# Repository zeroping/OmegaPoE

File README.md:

# OmegaPoE
A Power-over-Ethernet Dock for the Onion Omega board

This is a KiCad circut board design for an Onion Omega "dock" that connects the Onion via Ethernet, while also powering it via 802.3af Power-over-Ethernet.

The Onion Omega is a cheap ($10.75) linux single-board computer, and supports WiFi and Ethernet. For more information on the Onion Omega, see [the Onion Omega site](http://onion.io/omega2/).

This board is designed to be as small as possible while still providing an isolated 15-watt PoE supply. The 48 VDC power from PoE is converted into 12 V using a TI LM5070 in a flyback configuration. The 12 V is further stepped down to 5 V and 3.3 V using two TPS62135x DC-DC buck converters. 12 V was chosen to allow running 12V perhierals off of the board, such as 12V LED lighing strips. 

## Status
Four prototype boards have been built, and they work. There are some issues to work out and fixes to commit, but here's the v1 board run:

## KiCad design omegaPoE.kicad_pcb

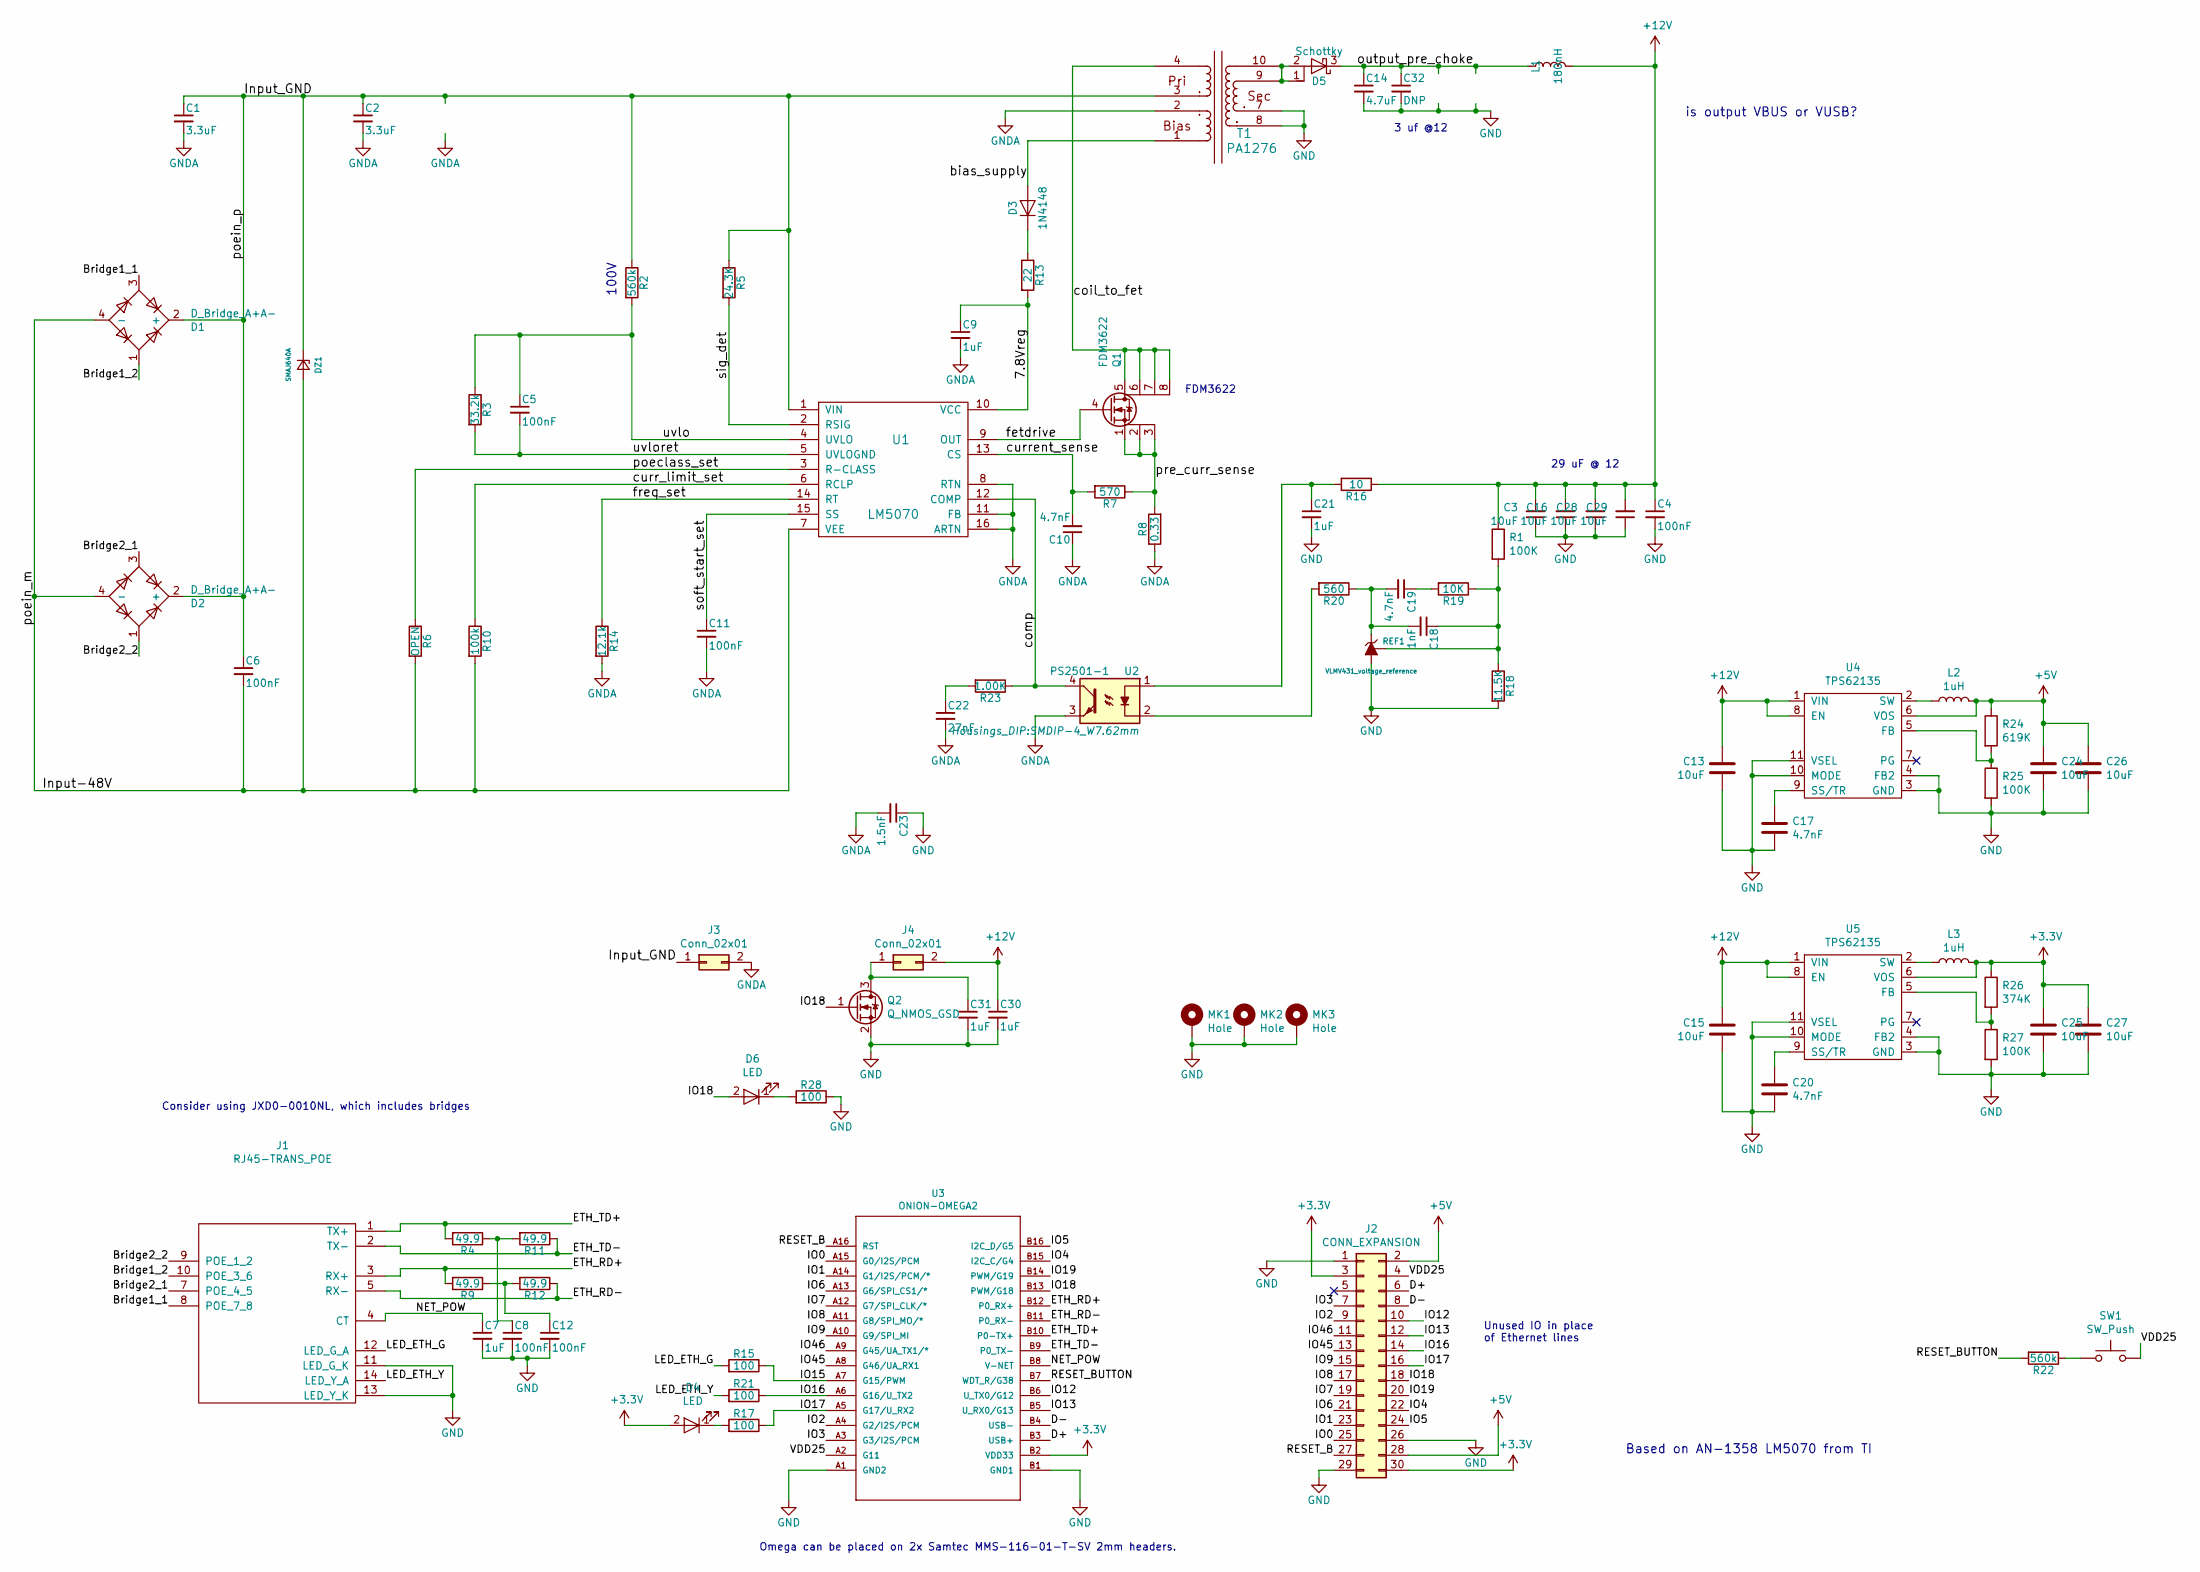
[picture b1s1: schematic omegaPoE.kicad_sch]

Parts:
C1, C2: 3.3uF; C_1206; MPN C3216X7S2A335K160AB
C3, C13, C15, C16, C24, C25, C26, C27, C28, C29: 10uF; C_1206; MPN MF-CAP-1206-10uF
C4, C5, C8, C11, C12: 100nF; C_0402; MPN MF-CAP-0402-0.1uF
C6: 100nF; C_1206; MPN 12061C104MAT4A
C7, C9, C21, C30, C31: 1uF; C_0402; MPN MF-CAP-0402-1uF
C10, C19: 4.7nF; C_0402; MPN MF-CAP-0402-4.7nF
C14: 4.7uF; C_0805; MPN EMK212ABJ475MG-T
C17, C20: 4.7nF; C_0402_NoSilk; MPN MF-CAP-0402-4.7nF
C18: 1nF; C_0402; MPN MF-CAP-0402-1nF
C22: 27nF; C_0603; MPN C0603C273K3RACTU
C23: 1.5nF; C_1206; MPN CC1206KKX7RDBB152
C32: DNP; C_1206; MPN DNP
D1, D2: D_Bridge_A+A-; U-DFN303-4; MPN SBR05M100BLP
D3: 1N4148; D_SOD-123; MPN MF-DIO-SOD123-1N4148
D4: LED; LED_0603; MPN MF-LED-0603-GREEN
D5: Schottky; TO-277A; MPN SS5P4-M3/86A
D6: LED; LED_reverse_gull; MPN LG T770-K1L2-1-Z
DZ1: SMAJ640A; D_SOD-123F; MPN SMF4L60A
J1: RJ45-TRANS_POE; JD0-0004NL; MPN JD0-0004NL
J2: CONN_EXPANSION; Pin_Header_Straight_2x15_Pitch2.54mm; MPN PPTC152LFBN-RC
J3, J4: Conn_02x01; Pin_Header_Straight_2x01_Pitch2.54mm
L1: 180nH; Murata-3000A-series; MPN 30201AC
L2, L3: 1uH; L_1210; MPN 1277AS-H-1R0M
MK1, MK2, MK3: Hole; MountingHole_2.2mm_M2_Pad_Via
Q1: FDM3622; DFN-8-1EP_3x3mm_Pitch0.65mm-mod; MPN FDM3622
Q2: Q_NMOS_GSD; SOT-23; MPN DMG2302UK-7
R1, R25, R27: 100K; R_0402_NoSilk; MPN RC0402FR-07100KL
R2, R22: 560k; R_0603; MPN MF-RES-0603-560K
R3: 33.2k; R_0402; MPN AC0402FR-0733K2L
R4, R9, R11, R12: 49.9; R_0603; MPN RC0603FR-0749R9P
R5: 24.3K; R_0603; MPN CRCW060324K3FKEA
R6: OPEN; R_0402
R7: 570; R_0402; MPN MF-RES-0402-560
R8: 0.33; R_0805; MPN RL0805FR-070R33L
R10: 100k; R_0402; MPN MF-RES-0402-100K
R13: 22; R_0402; MPN MF-RES-0402-22
R14: 12.1k; R_0402; MPN AC0402FR-0712K1L
R15, R17, R21, R28: 100; R_0402; MPN MF-RES-0402-100
R16: 10; R_0402; MPN MF-RES-0402-10
R18: 11.5K; R_0402; MPN RC0402FR-0711K5L
R19: 10K; R_0402; MPN MF-RES-0402-10K
R20: 560; R_0402; MPN MF-RES-0402-560K
R23: 1.00K; R_0402; MPN MF-RES-0402-1K
R24: 619K; R_0402_NoSilk; MPN RC0402FR-07619KL
R26: 374K; R_0402_NoSilk; MPN RC0402FR-07374KL
REF1: VLMV431_voltage_reference; SOT-23; MPN LMV431AIM
SW1: SW_Push; SW_SPST_KMR2; MPN MF-SW-TACT-4.2MM
T1: PA1276; Pulse_PA1269; MPN C1586
U1: LM5070; TSSOP-16_4.4x5mm_Pitch0.65mm; MPN LM5070MTCX-50
U2: PS2501-1; SMDIP-4_W7.62mm; MPN PS2501L-1
U3: ONION-OMEGA2; ONION-OMEGA; MPN DNP
U4, U5: TPS62135; DFN-8-3EP_3x2mm_Pitch0.5mm; MPN TPS621351

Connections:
+3V3: C25.1, C27.1, D4.2 (A), J2.3, J2.30, L3.2, R26.1, U3.B2 (VDD33), U5.6 (VOS)
+5V: C24.1, C26.1, J2.2, J2.28, L2.2, R24.1, U4.6 (VOS)
+12V: C3.2, C4.1, C13.2, C15.2, C16.2, C28.2, C29.2, C30.1, J4.2, L1.2, R1.1, R16.1, U4.1 (VIN), U4.8 (EN), U5.1 (VIN), U5.8 (EN)
/7.8Vreg: C9.1, R13.2, U1.10 (VCC)
/Bridge1_1: D1.3, J1.8 (POE_7_8)
/Bridge1_2: D1.1, J1.10 (POE_3_6)
/Bridge2_1: D2.3, J1.7 (POE_4_5)
/Bridge2_2: D2.1, J1.9 (POE_1_2)
/D+: J2.6, U3.B3 (USB+)
/D-: J2.8, U3.B4 (USB-)
/ETH_RD+: J1.3 (RX+), R9.2, U3.B12 (P0_RX+)
/ETH_RD-: J1.5 (RX-), R12.1, U3.B11 (P0_RX-)
/ETH_TD+: J1.1 (TX+), R4.2, U3.B10 (P0-TX+)
/ETH_TD-: J1.2 (TX-), R11.1, U3.B9 (P0_TX-)
/IO0: J2.25, U3.A15 (G0/I2S/PCM)
/IO1: J2.23, U3.A14 (G1/I2S/PCM/*)
/IO2: J2.9, U3.A4 (G2/I2S/PCM)
/IO3: J2.7, U3.A3 (G3/I2S/PCM)
/IO4: J2.22, U3.B15 (I2C_C/G4)
/IO5: J2.24, U3.B16 (I2C_D/G5)
/IO6: J2.21, U3.A13 (G6/SPI_CS1/*)
/IO7: J2.19, U3.A12 (G7/SPI_CLK/*)
/IO8: J2.17, U3.A11 (G8/SPI_MO/*)
/IO9: J2.15, U3.A10 (G9/SPI_MI)
/IO12: J2.10, U3.B6 (U_TX0/G12)
/IO13: J2.12, U3.B5 (U_RX0/G13)
/IO15: R15.1, U3.A7 (G15/PWM)
/IO16: J2.14, R21.1, U3.A6 (G16/U_TX2)
/IO17: J2.16, R17.1, U3.A5 (G17/U_RX2)
/IO18: D6.2 (A), J2.18, Q2.1 (G), U3.B13 (PWM/G18)
/IO19: J2.20, U3.B14 (PWM/G19)
/IO45: J2.13, U3.A8 (G46/UA_RX1)
/IO46: J2.11, U3.A9 (G45/UA_TX1/*)
/Input-48V: C6.2, D1.4 (-), D2.4 (-), DZ1.2 (A), R6.2, R10.2, U1.7 (VEE)
/Input_GND: C1.1, C2.1, C6.1, D1.2 (+), D2.2 (+), DZ1.1 (K), J3.1, R2.1, R5.1, T1.3, U1.1 (VIN)
/LED_ETH_G: J1.12 (LED_G_A), R15.2
/LED_ETH_Y: J1.14 (LED_Y_A), R21.2
/NET_POW: C7.1, J1.4 (CT), U3.B8 (V-NET)
/RESET_B: J2.27, U3.A16 (RST)
/RESET_BUTTON: R22.2, U3.B7 (WDT_R/G38)
/VDD25: J2.4, SW1.2, U3.A2 (G11)
/bias_supply: D3.2 (A), T1.1
/coil_to_fet: Q1.5 (D), Q1.6 (D), Q1.7 (D), Q1.8 (D), T1.4
/comp: R23.1, U1.12 (COMP), U2.4
/curr_limit_set: R10.1, U1.6 (RCLP)
/current_sense: C10.2, R7.2, U1.13 (CS)
/fetdrive: Q1.4 (G), U1.9 (OUT)
/freq_set: R14.1, U1.14 (RT)
/output_pre_choke: C14.1, C32.1, D5.3 (K), L1.1
/poeclass_set: R6.1, U1.3 (R-CLASS)
/pre_curr_sense: Q1.1 (S), Q1.2 (S), Q1.3 (S), R7.1, R8.2
/sig_det: R5.2, U1.2 (RSIG)
/soft_start_set: C11.1, U1.15 (SS)
/uvlo: C5.1, R2.2, R3.1, U1.4 (UVLO)
/uvloret: C5.2, R3.2, U1.5 (UVLOGND)
GND: C3.1, C4.2, C7.2, C8.2, C12.2, C13.1, C14.2, C15.1, C16.1, C17.2, C20.2, C21.2, C23.1, C24.2, C25.2, C26.2, C27.2, C28.1, C29.1, C30.2, C31.2, C32.2, J1.11 (LED_G_K), J1.13 (LED_Y_K), J2.1, J2.26, J2.29, MK1.1, MK2.1, MK3.1, Q2.2 (S), R18.2, R25.2, R27.2, R28.1, REF1.3 (A), T1.7, T1.8, U3.A1 (GND2), U3.B1 (GND1), U4.3 (GND), U4.4 (FB2), U4.10 (MODE), U4.11 (VSEL), U5.3 (GND), U5.4 (FB2), U5.10 (MODE), U5.11 (VSEL)
GNDA: C1.2, C2.2, C9.2, C10.1, C11.2, C22.2, C23.2, J3.2, R8.1, R14.2, T1.2, U1.8 (RTN), U1.11 (FB), U1.16 (ARTN), U2.3
unnamed: C8.1, R4.1, R11.2
unnamed: C12.1, R9.1, R12.2
unnamed: C17.1, U4.9 (SS/TR)
unnamed: C18.1, R1.2, R18.1, R19.1, REF1.1 (REF)
unnamed: C18.2, C19.2, R20.1, REF1.2 (K)
unnamed: C19.1, R19.2
unnamed: C20.1, U5.9 (SS/TR)
unnamed: C21.1, R16.2, U2.1
unnamed: C22.1, R23.2
unnamed: C31.1, J4.1, Q2.3 (D)
unnamed: D3.1 (K), R13.1
unnamed: D4.1 (K), R17.2
unnamed: D5.1 (A), D5.2 (A), T1.9, T1.10
unnamed: D6.1 (K), R28.2
unnamed: L2.1, U4.2 (SW)
unnamed: L3.1, U5.2 (SW)
unnamed: R20.2, U2.2
unnamed: R22.1, SW1.1
unnamed: R24.2, R25.1, U4.5 (FB)
unnamed: R26.2, R27.1, U5.5 (FB)

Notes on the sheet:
Omega can be placed on 2x Samtec MMS-116-01-T-SV 2mm headers.
FDM3622
Consider using JXD0-0010NL, which includes bridges
100V
Based on AN-1358 LM5070 from TI
is output VBUS or VUSB?
Unused IO in place of Ethernet lines
3 uf @12
29 uF @ 12

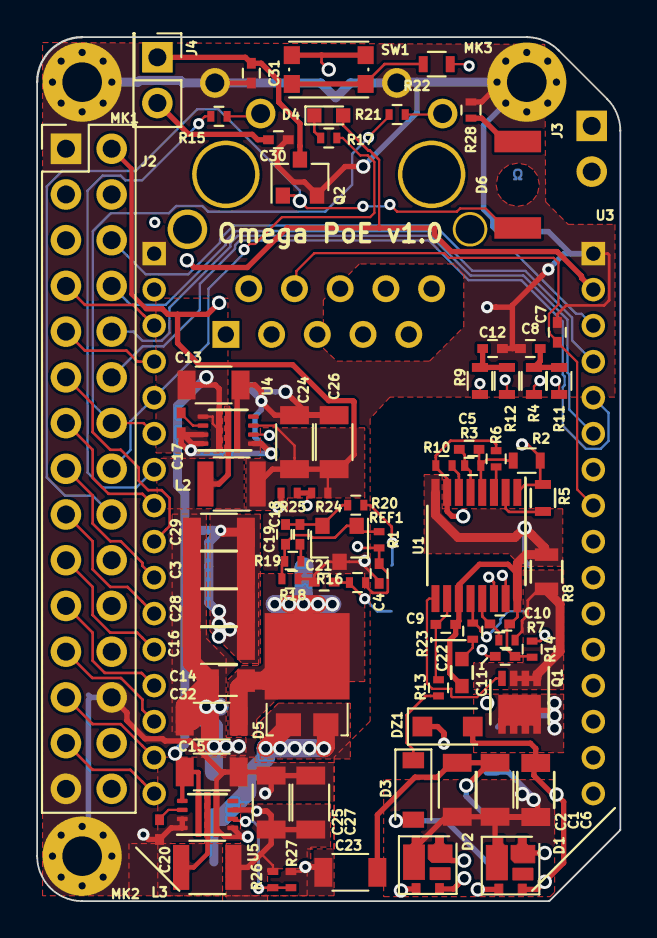
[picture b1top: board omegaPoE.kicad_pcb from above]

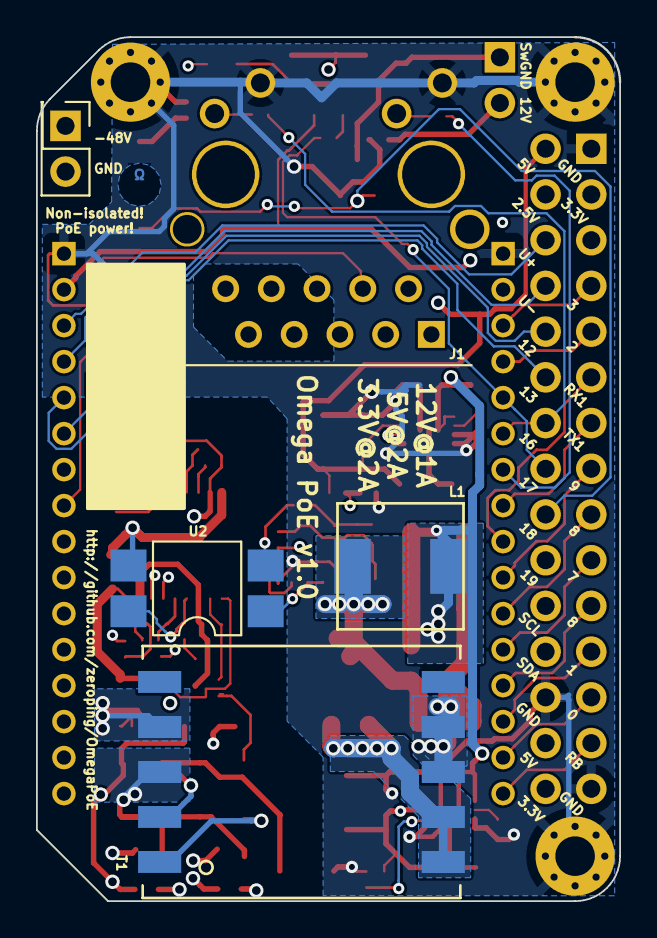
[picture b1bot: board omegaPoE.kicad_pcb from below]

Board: 4 copper layers, 32.4 x 48.0 mm, 87 parts (5 on the bottom side), 77 nets.

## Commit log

2018-06-07 Initial commit of partly-finished board
2018-06-07 More cleanup, some power planes in and text fixed
2018-06-07 Mostly finished with design. Fixed lots of 3D models and some part rotations.
2018-06-09 Swapped to some cheaper parts, fixed cap selection on 12V line.
2018-06-10 Added mounting holes, shrank up board, make 12V output switched
2018-06-10 Added silkscreen
2018-06-10 Added renders
2018-06-10 Adding renders to Readme
2018-06-11 More cleanup. Fixing silkscreen on footprints, cleaing up MPN's.
2018-06-11 Moved flyback output components to minimize EMI. Lots of power flood work.
2018-06-11 Not sure what changed - more zone cleanup, I think?
2018-06-12 Added rever-semount LED for testing, cleaned up MPN listings some more.
2018-06-12 Final updates before ordering
2018-08-06 Added photo renders
2023-07-10 Updated to kicad7
